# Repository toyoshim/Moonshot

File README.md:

# Moonshot
USB to Legacy Joystick port converter.

# License
The 3-Clause BSD License is applied for project specific all resources under
docs, firmware, and tools directories. See LICENSE.bsd3 for details.

Creative Commons NonCommercial license is applied for project specific all
resources under KiCAD directory. See LICENSE.cc_by_nc for details.

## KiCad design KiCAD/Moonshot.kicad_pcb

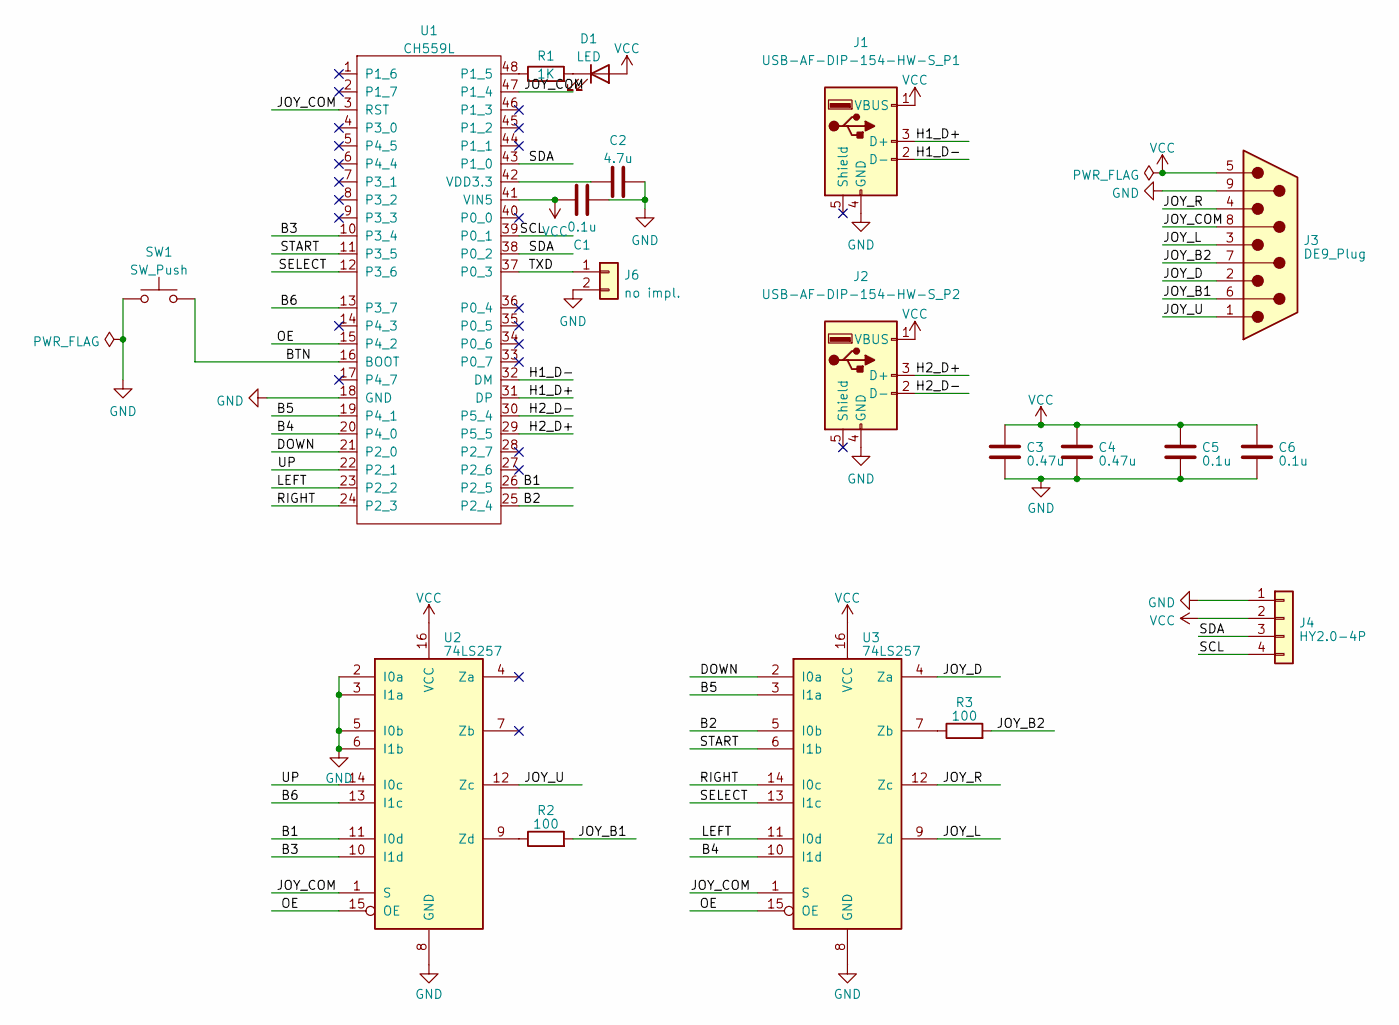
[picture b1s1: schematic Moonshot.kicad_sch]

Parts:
C1, C5, C6: 0.1u; C_0402_1005Metric
C2: 4.7u; C_0402_1005Metric
C3, C4: 0.47u; C_0402_1005Metric
D1: LED; LED_0603_1608Metric_Pad1.05x0.95mm_HandSolder; LCSC C965807
J1: USB-AF-DIP-154-HW-S_P1; USB-A-TH_JTJ-USB-A-F-10.0-010; LCSC C42576
J2: USB-AF-DIP-154-HW-S_P2; USB-A-TH_JTJ-USB-A-F-10.0-010; LCSC C42576
J3: DE9_Plug; DSUB-9_Female_TE_2301844_1; LCSC C3135162
J4: HY2.0-4P; CONN-TH_4P-P2.00_HX20020-4A_2; LCSC C7429580
J6: no impl.; PinHeader_2x01_P2.54mm_Vertical
R1: 1K; R_0402_1005Metric
R2, R3: 100; R_0402_1005Metric
SW1: SW_Push; TS-1159B; LCSC C381055
U1: CH559L; LQFP-48_7x7mm_P0.5mm; LCSC C150548
U2, U3: 74LS257; TSSOP-16_4.4x5mm_P0.65mm; LCSC C2868824

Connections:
/B1: U1.26 (P2_5), U2.11 (I0d)
/B2: U1.25 (P2_4), U3.5 (I0b)
/B3: U1.10 (P3_4), U2.10 (I1d)
/B4: U1.20 (P4_0), U3.10 (I1d)
/B5: U1.19 (P4_1), U3.3 (I1a)
/B6: U1.13 (P3_7), U2.13 (I1c)
/BTN: SW1.2, U1.16 (BOOT)
/DOWN: U1.21 (P2_0), U3.2 (I0a)
/H1_D+: J1.3 (D+), U1.31 (DP)
/H1_D-: J1.2 (D-), U1.32 (DM)
/H2_D+: J2.3 (D+), U1.29 (P5_5)
/H2_D-: J2.2 (D-), U1.30 (P5_4)
/JOY_B1: J3.6, R2.2
/JOY_B2: J3.7, R3.2
/JOY_COM: J3.8, U1.3 (RST), U1.47 (P1_4), U2.1 (S), U3.1 (S)
/JOY_D: J3.2, U3.4 (Za)
/JOY_L: J3.3, U3.9 (Zd)
/JOY_R: J3.4, U3.12 (Zc)
/JOY_U: J3.1, U2.12 (Zc)
/LEFT: U1.23 (P2_2), U3.11 (I0d)
/OE: U1.15 (P4_2), U2.15 (OE), U3.15 (OE)
/RIGHT: U1.24 (P2_3), U3.14 (I0c)
/SCL: J4.4, U1.39 (P0_1)
/SDA: J4.3, U1.38 (P0_2), U1.43 (P1_0)
/SELECT: U1.12 (P3_6), U3.13 (I1c)
/START: U1.11 (P3_5), U3.6 (I1b)
/TXD: J6.1, U1.37 (P0_3)
/UP: U1.22 (P2_1), U2.14 (I0c)
GND: C1.2, C2.2, C3.2, C4.2, C5.2, C6.2, J1.4 (GND), J2.4 (GND), J3.9, J4.1, J6.2, SW1.1, U1.18 (GND), U2.2 (I0a), U2.3 (I1a), U2.5 (I0b), U2.6 (I1b), U2.8 (GND), U3.8 (GND)
unnamed: D1.1 (K), R1.2
unnamed: R1.1, U1.48 (P1_5)
unnamed: C2.1, U1.42 (VDD3.3)
unnamed: R2.1, U2.9 (Zd)
unnamed: R3.1, U3.7 (Zb)
VCC: C1.1, C3.1, C4.1, C5.1, C6.1, D1.2 (A), J1.1 (VBUS), J2.1 (VBUS), J3.5, J4.2, U1.41 (VIN5), U2.16 (VCC), U3.16 (VCC)

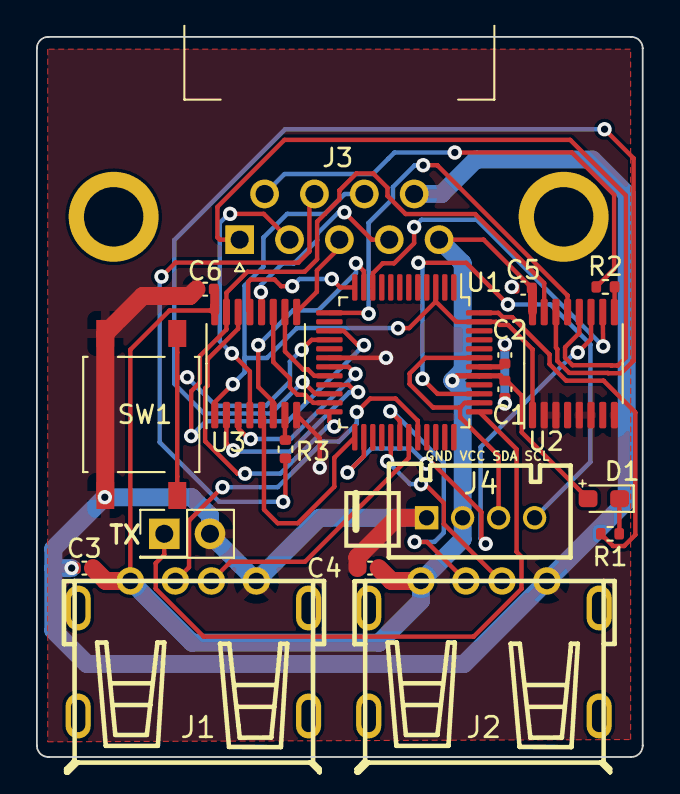
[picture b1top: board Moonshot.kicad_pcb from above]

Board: 2 copper layers, 33.7 x 40.0 mm, 19 parts (0 on the bottom side), 35 nets.

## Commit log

2023-10-16 firmware
2023-10-21 tentative 6b support (not stable yet)
2023-10-22 firmware v0.95
2023-10-22 rev2 pcb
2023-10-23 rename KiCAD files
2023-10-23 rapid fire implementation
2023-10-23 cyberstick mode
2023-10-24 adjust data valid period as x68k seems failing to take data sometime
2023-10-26 select+start support
2023-10-27 support page
2023-10-27 Add an empty README.md at the top directory
2023-10-27 split setting per mode
2023-10-27 stabilize cyberstick mode under unsupported situation (com is low)
2023-10-27 0.98
2023-10-28 update firmware default data set
2023-10-28 fix data write logic
2023-10-28 chlib roll with debug code
2023-10-31 0.99 for proto1 and proto2
2023-10-31 0.99 doc
2023-11-08 0.99.1 introduce minimum count limit in the cyberstick protocol
2023-11-08 update README.md to clarify board types
2023-11-09 submit missed firmware binaries
2023-11-14 release high-priority interrupt only when the request reaches timeout
2023-11-17 implement MD mode (but not stable yet)
2023-11-17 chlib roll
2023-11-17 0.99.2
2023-11-18 v0.99.2
2023-11-21 MD 6B support is now stable
    Confirmed with SF-II/MD and CPMD.X/X68k.
2023-11-21 register 0.99.3
2023-11-22 0.99.4, MD6B for MJIC4
2023-11-23 0.99.5 longer timeout
2023-11-23 0.99.6, timeout x4
2023-11-24 0.99.7
2023-11-25 v3 pcb
2023-11-25 i2c tentative support (unstable)
2023-11-26 crlf -> lf
2023-11-26 stabilize i2c support
    - chrlib roll and use exclusive_time feature
    - check if the interrupt was for the handler more precisely on each case
    - pull-up COM pin
2023-12-01 implement extended cyberstick protocol for bidi communication
2023-12-01 remove coin count code
2023-12-01 remove mahjong support
2023-12-01 remove rotary and screen support
2023-12-01 remove unused controller code
2023-12-01 remove debug code
2023-12-01 implement raw data commands
2023-12-01 use raw data for I2C
2023-12-01 update moonshot protocol handler
2023-12-01 bug fixes
2023-12-02 remove arcade specific settings
2023-12-02 remove unused settings
2023-12-02 revise flash code to use chlib library
2023-12-02 move led ownership from settings to main
2023-12-02 settings: ms68 format support
2023-12-02 split command
2023-12-02 protocol implementation done, but not verified yet
2023-12-02 controller: cleanup
2023-12-02 bug fix: should accept 0xff while transaction
2023-12-02 bug fix: should terminate transaction mode on their completion
2023-12-02 use static rather than stack for the flash write buffer
2023-12-02 fix for prot2 board
2023-12-02 bug fix on settings migration
2023-12-02 bug fix: rapid fire off didn't work
2023-12-05 layout tool for x68k
2023-12-05 submit msconf executable
2023-12-06 publish as 0.99.8
2023-12-06 add images
2023-12-06 use jekyll's annotation for the centering
2023-12-10 0.99.9
    Modify cyberstick's timeout behavior.
    Moonshot just ignored if the request is stuck at low, but to follow
    the original cyberstick behavior, now it starts sending data
    at 25us per half a cycle speed. This is needed for some titles
    that detects cyberstick existence automatically. They hold the request
    low, and see if the response arrived within the next 100us.
2023-12-10 document update - link for the x68k layout tool
2023-12-11 Implement Faces compatible I2C interface at address 0x08
2023-12-11 0.99.10
2023-12-13 msconf.x performance optimization
2023-12-13 msconf: cleanup
2023-12-14 port layout tool frontend for the web site
2023-12-15 tentative CDC mode impl
2023-12-16 update msconf wasm version
2023-12-16 update cdc
2023-12-16 modify cdc client code to follow the latest api
2023-12-16 msconf/wasm is now stable
2023-12-17 change the timeout value for the cdc/host mode detection
    It seems the counter is wrapped within 0x4000?
    Didn't check, but 0x4000 counter causes infinite loop
2023-12-17 MSX0 I2C access support
    It needs to connect Moonshot to MSX0's internal I2C
    on starting the MSX emulator.
2023-12-18 remove iona setting support
2023-12-18 polish settings
2023-12-18 remove intermediate layout format
2023-12-18 safe mode
2023-12-18 split mode change mode
2023-12-18 save/load mode
2023-12-18 bug fix: new_mode = mode + 1
2023-12-18 commands: split commit, and add mode change
2023-12-18 use local variable rather than volatile
2023-12-19 update msconf
2023-12-20 commit config on initial preset load
2023-12-20 force usb bus reset to detect initially connected devices
2023-12-20 firmware v1.00.0
2023-12-20 tool update
2023-12-21 cyberstick timeout cleanup
2023-12-21 msconf.x v1.00.0
2023-12-21 msconf: layout fix
2023-12-21 msconf/wasm: 1.00.1 port done
2023-12-21 command cleanup to prepare using multiple address spaces
2023-12-22 import 10bit support code from iona-us
    now with the latest chlib, it can support GT Force Pro.
2023-12-26 update documents
2023-12-26 add _includes
2023-12-26 update firmware document to add more tips
2023-12-28 Moonshot rev.4 board
2023-12-29 fix the product # from 17 to 14
2024-01-09 replace draft.pdf
2024-01-30 Rev.5 board
2024-01-30 fw 1.00.1
2024-04-30 PCB Rev.7
2024-04-30 extended protocol bug fix
    From the last fix for the 1.00.1, msconf.x doesn't work for
    false interrupt triggered for nested com signal edges.
2024-04-30 Add Libble Rabble mode
2024-04-30 move safe mode to minor mode
    to enter the minor mode, users need to press the button for
    more than 1 second. otherwise, the mode is skipped.
2024-04-30 msconf.x 1.01.0
2024-04-30 update online msconf
2024-04-30 update document
2024-05-01 Clarify licenses
2024-07-09 update shop.md to mention くにちこ&たんぼ's case
2025-02-12 update kicad proj
2025-02-14 v1.02.0
2025-02-22 msconf: bug fix on select/start button indicators
    Update to 1.02.1.
    In the previous version, output indicator mistakenly showed
    select and start button has been swapped.
2025-03-20 cross build with XDEV68K
2025-03-21 minimum support for layout mapper for Z
2025-03-21 mapper mode bug fix
    - pointers should be `volatile`s
    - cyber_map should be negative logic
2025-03-22 more bug fixes on mapper mode
    this is a kind of stable release for the early prototype
    of the Joypad Mapper for Z.
2025-09-06 msconf.c: CRLF -> LF
2025-09-06 Fix a typo, conf`u`guration -> conf`i`guration
    Also minor fixes to compile them with GCC/X68k (mariko)
2025-09-06 Update msconf.x binary
